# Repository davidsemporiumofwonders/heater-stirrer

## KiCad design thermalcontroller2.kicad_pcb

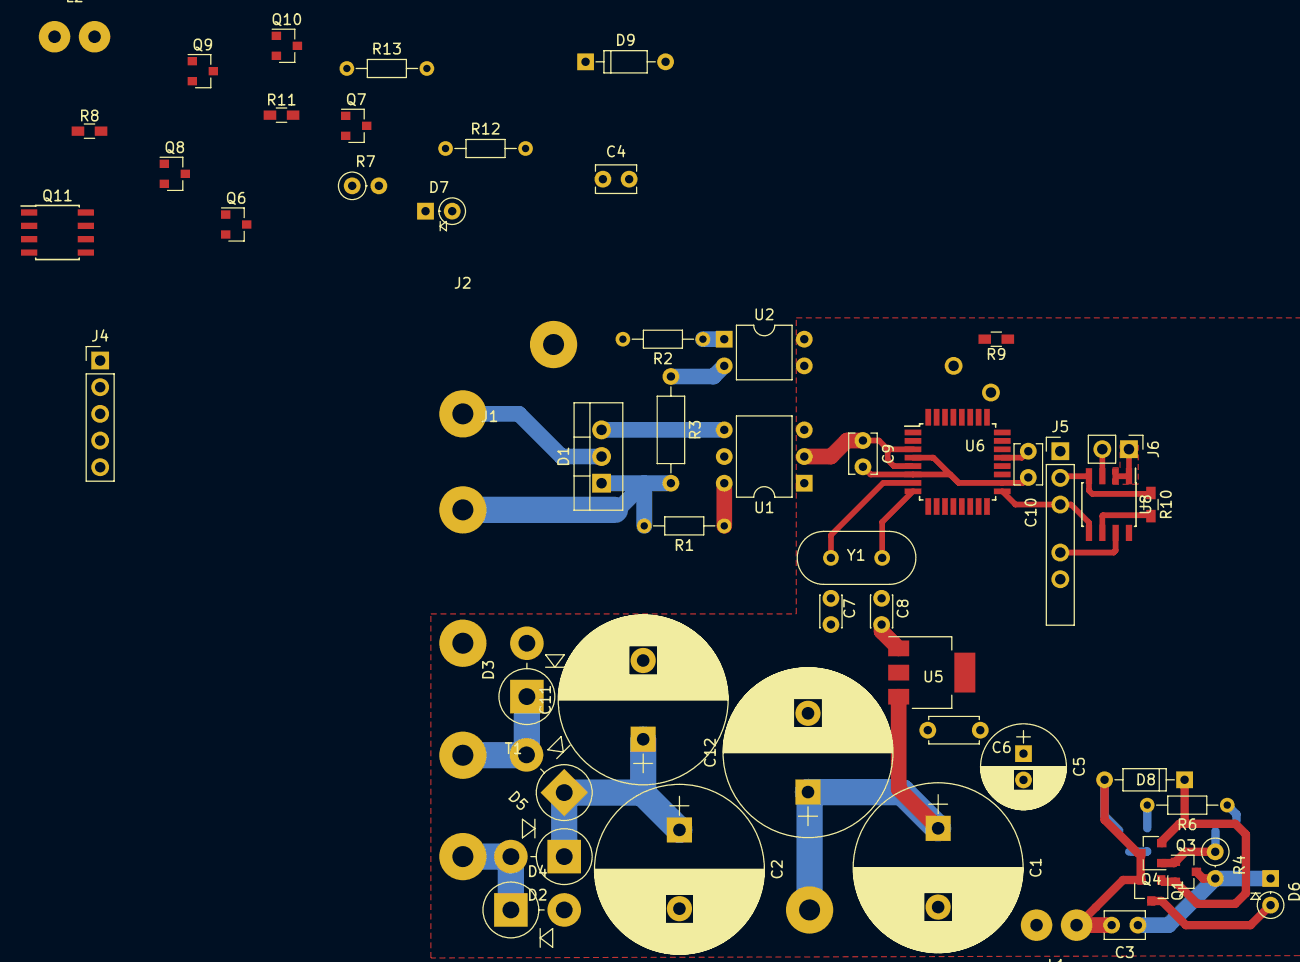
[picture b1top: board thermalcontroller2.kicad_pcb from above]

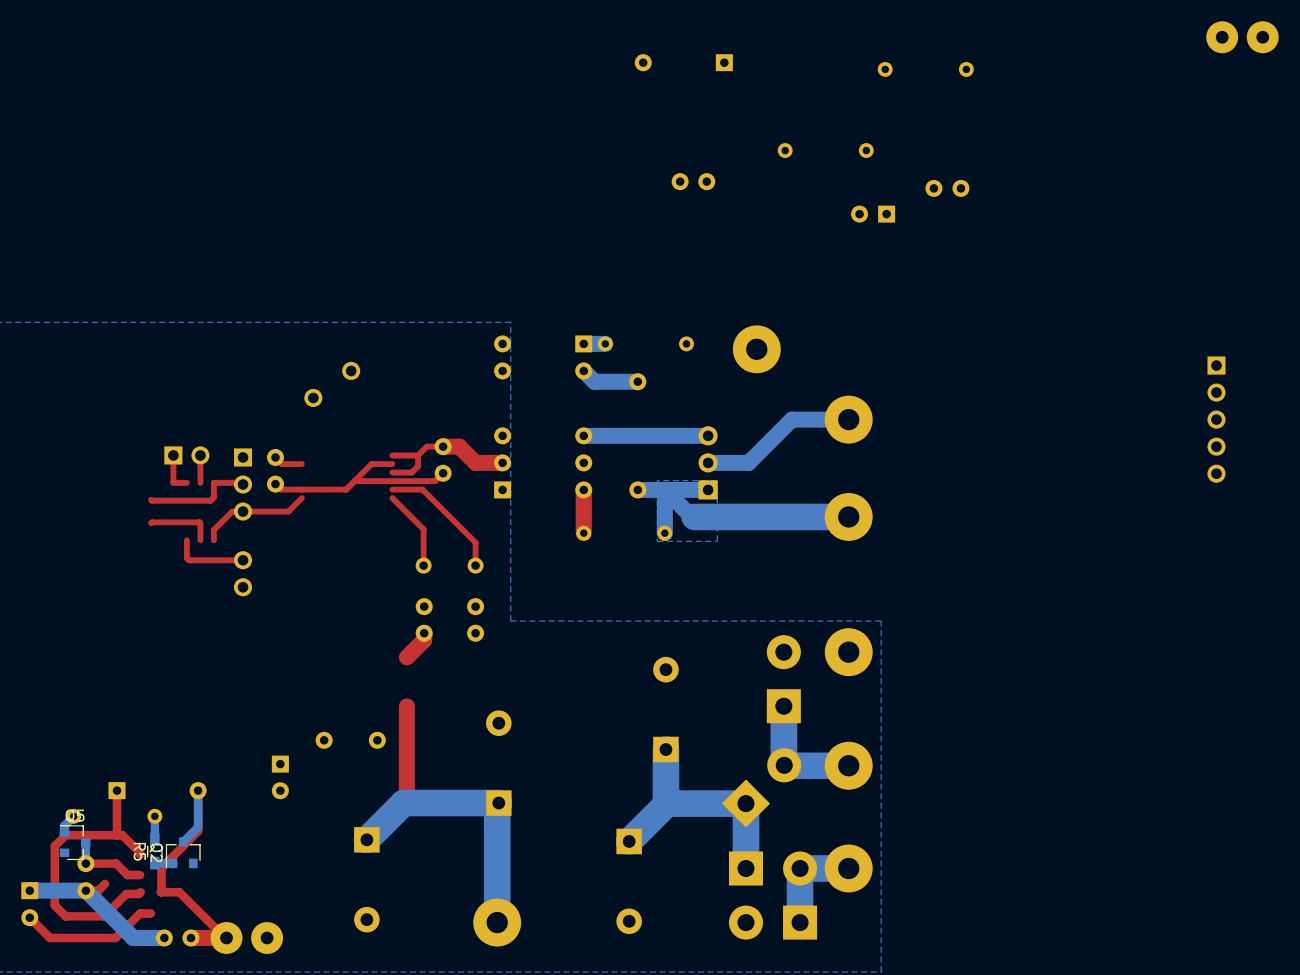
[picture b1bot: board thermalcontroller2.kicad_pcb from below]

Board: 2 copper layers, 59 parts (3 on the bottom side), 44 nets.

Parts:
C1, C2, C11, C12: 4700μ; CP_Radial_D16.0mm_P7.50mm
C3, C4: 47n; C_Disc_D3.8mm_W2.6mm_P2.50mm
C5: 220μ; CP_Radial_D8.0mm_P2.50mm
C6: 1μ; C_Disc_D4.7mm_W2.5mm_P5.00mm
C7, C8: 22p; C_Disc_D3.0mm_W2.0mm_P2.50mm
C9, C10: 100n; C_Disc_D3.8mm_W2.6mm_P2.50mm
D1: BTA_16; TO-220-3_Vertical
D2, D3, D4, D5: 1N5400; D_DO-201AD_P5.08mm_Vertical_AnodeUp
D6, D7: 1N4148; D_DO-35_SOD27_P2.54mm_Vertical_KathodeUp
D8, D9: Zener-10v; D_DO-35_SOD27_P7.62mm_Horizontal
J1: Conn_01x02; SolderWirePad_2x_2mmDrill
J2: Conn_01x03; SolderWirePad_3x_2mmDrill
J4: Conn_01x05; Pin_Header_Straight_1x05_Pitch2.54mm
J5: Conn_01x07; Pin_Header_Straight_1x07_Pitch2.54mm
J6: Conn_01x02; Pin_Header_Straight_1x02_Pitch2.54mm
L1, L2: solenoid; SolderWirePad_2x_1-2mmDrill
Q1, Q2, Q6, Q7: AO3400; SOT-23
Q3, Q8: MMBT3904; SOT-23
Q4, Q9: MMBT3906; SOT-23
Q5, Q10: BSS138; SOT-23
Q11: FDS4465; SOIC-8_3.9x4.9mm_Pitch1.27mm
R1, R6, R12, R13: 330; R_Axial_DIN0204_L3.6mm_D1.6mm_P7.62mm_Horizontal
R2: 68k; R_Axial_DIN0204_L3.6mm_D1.6mm_P7.62mm_Horizontal
R3: 68k; R_Axial_DIN0207_L6.3mm_D2.5mm_P10.16mm_Horizontal
R4, R7: 22k; R_Axial_DIN0207_L6.3mm_D2.5mm_P2.54mm_Vertical
R5, R8: 330; R_0603_HandSoldering
R9, R10: 10k; R_0603_HandSoldering
R11: 1Meg; R_0603_HandSoldering
T1: Transformer_1P_SS; SolderWirePad_4xInline_2mmDrill
U1: MOC3052M; DIP-6_W7.62mm
U2: LTV-814; DIP-4_W7.62mm
U5: AMS1117-5; SOT-223-3_TabPin2
U6: ATMEGA88PA-AU; TQFP-32_7x7mm_Pitch0.8mm
U8: MAX6675; SOIC-8_3.9x4.9mm_Pitch1.27mm
Y1: 16MHz; Crystal_HC49-U_Vertical

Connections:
+12V: C1.1, C12.1, Q11.5, T1.4, U5.3
+24V: C2.1, C11.1, D2.1, D5.1, D6.2, D7.2, Q1.3, Q6.3
+VSW: L1.2, L2.2, Q11.1, R11.2
GND: C1.2, C2.2, C5.2, C6.2, C7.1, C8.1, C9.1, C10.1, C11.2, C12.2, D3.2, D4.2, J2.3, J4.5, J5.1, J6.1, Q2.2, Q5.2, Q7.2, Q10.2, U1.2, U2.3, U5.1, U6.3, U6.5, U6.21, U8.1, U8.2
unnamed: C3.1, D6.1, Q3.3, R4.2
unnamed: C3.2, D8.2, L1.1, Q1.2, Q2.3, Q4.3
unnamed: C4.1, D7.1, Q8.3, R7.2
unnamed: C4.2, D9.2, L2.1, Q6.2, Q7.3, Q9.3
unnamed: C7.2, U6.7, Y1.1
unnamed: C8.2, U6.8, Y1.2
unnamed: D1.1, J2.1, R1.2, R3.2
unnamed: D1.2, J1.1
unnamed: D1.3, U1.4
unnamed: D2.2, D4.1, T1.5
unnamed: D3.1, D5.2, T1.3
unnamed: D8.1, Q1.1, Q3.2, Q4.2
unnamed: D9.1, Q6.1, Q8.2, Q9.2
unnamed: J2.2, R2.2
unnamed: J4.1, U6.28
unnamed: J4.2, U6.31
unnamed: J4.3, U6.1
unnamed: J5.3, U6.15
unnamed: J5.4, U6.16, U8.7
unnamed: J5.5, U6.17, U8.5
unnamed: J5.6, U6.26
unnamed: J5.7, U6.29
unnamed: J6.2, U8.3
unnamed: Q2.1, R5.1
unnamed: Q3.1, Q4.1, Q5.3, R4.1
unnamed: Q5.1, R6.1
unnamed: Q7.1, R12.1
unnamed: Q10.1, R13.1
unnamed: Q8.1, Q9.1, Q10.3, R7.1
unnamed: R1.1, U1.6
unnamed: R2.1, U2.1
unnamed: R3.1, U2.2
unnamed: R5.2, R6.2, U6.10
unnamed: R8.1, U1.1
unnamed: R8.2, U6.14
unnamed: R9.2, U2.4, U6.32
unnamed: R10.2, U6.13, U8.6
unnamed: R12.2, R13.2, U6.9
VCC: C5.1, C6.1, C9.2, C10.2, J4.4, J5.2, R9.1, R10.1, U5.2, U6.4, U6.6, U6.18, U8.4
en: Q11.4, R11.1, U6.11
